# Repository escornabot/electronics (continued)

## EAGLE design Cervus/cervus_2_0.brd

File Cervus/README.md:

# Cervus 2.001

## Catalog

- [Cervus][KEY01] (by [Xdesig][XDE01]) is a 50x50mm board, it controls any Escornabot, and is an atmega development PCB (Arduino Leonardo compatible)

## License

Every content in this repo, otherwise specified under subdirectories, is
licensed under [Creative Commons BY-SA](LICENSE).

## To buy boards

Developers don't produce boards to sell. Under [PCBWAY]

[KEY01]: Keypad
[PCBWAY]: https://www.pcbway.com/project/shareproject/Cervus_Arduino_Leonardo_Coompatible.html
[XDE01]: https://twitter.com/xdesig

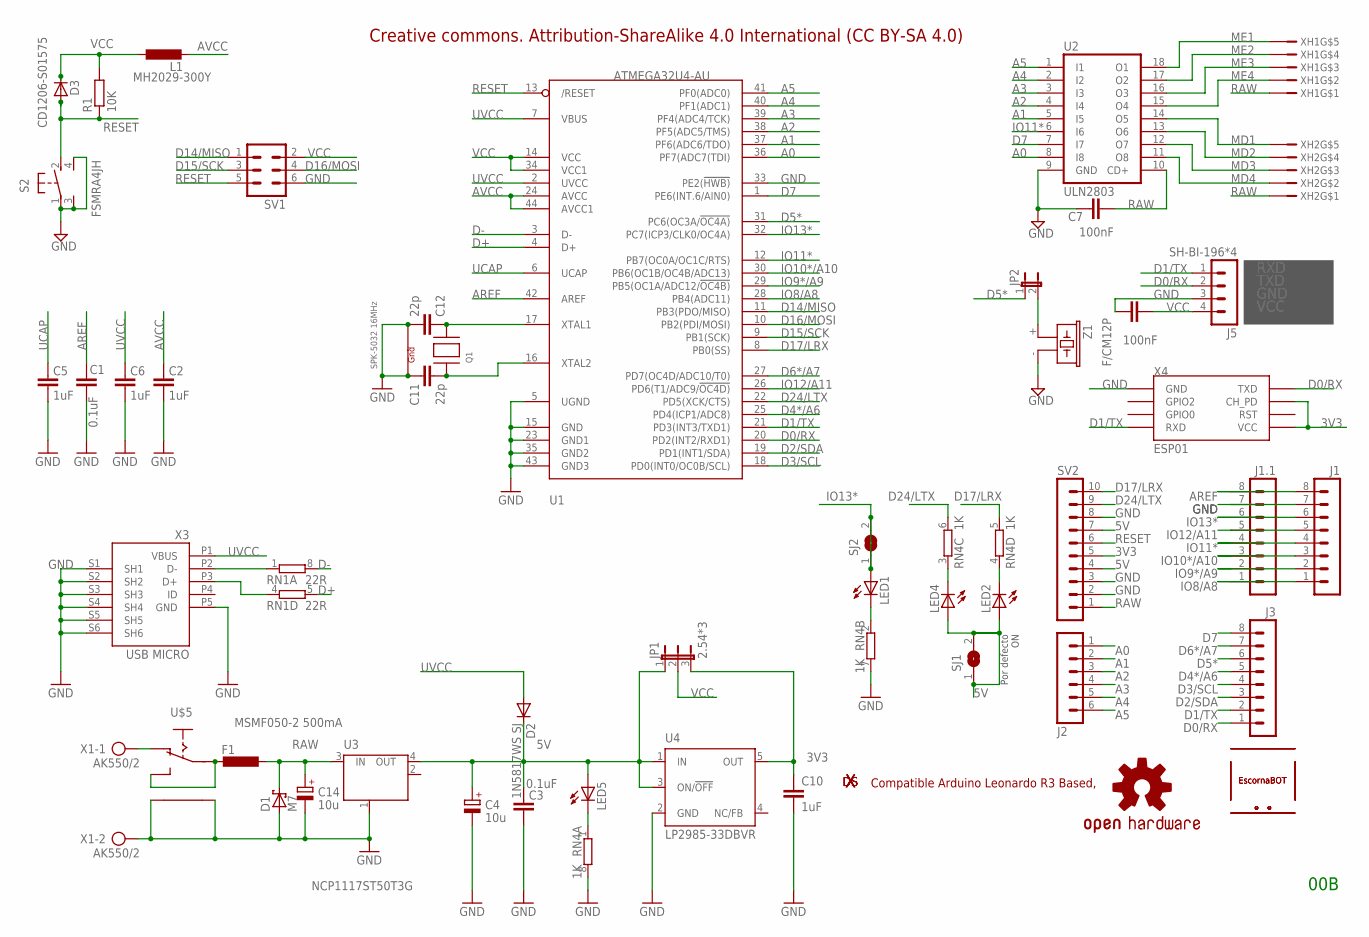
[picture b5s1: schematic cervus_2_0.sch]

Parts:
C1, C3: 0.1uF; 0603-CAP
C2, C5, C6, C10: 1uF; 0603-CAP
C4, C14: 10u; SMC_B
C7, C8: 100nF; C0603K
C11, C12: 22p; C0603-ROUND
D1: M7; SMA
D2: 1N5817WS SJ; SOD-323
D3: CD1206-S01575; MINIMELF
F1: MSMF050-2 500mA; L1812
J1, J1.1, J3: MA08-1
J2: MA06-1
J5: SH-BI-196*4; MA04-1
JP1: 2.54*3; JP2
JP2: JP1E; JP1
L1: MH2029-300Y; R0805
LED1, LED2, LED4, LED5: LEDCHIPLED_0603; CHIPLED_0603
LOGO1: OSHW-LOGOS; OSHW-LOGO-S
Q1: SPK-5032 16MHz; NX3225
R1: 10K; R0603
RN1: 22R; CAY16
RN4: 1K; CAY16
S2: FSMRA4JH; B3F-31XX
SJ1, SJ2: SJ
SV1: MA03-2
SV2: MA10-1
U1: ATMEGA32U4-AU; TQFP44
U2: ULN2803; DIL18
U3: NCP1117ST50T3G; SOT223
U4: LP2985-33DBVR; SOT23-DBV
U$1, U$2: XDESIG; XDESIG_CU_2
U$3, U$4: ESCORNABOT; ESCORNA_PEQUE
U$5: ESCORNA_SK12F14D; ESCORNA_SK-12D07
X1: AK550/2
X3: USB MICRO; CON2_USB_MICRO_B_AT
X4: ESP01
XH1, XH2: XH2.54-5P; B5B-XH-A
Z1: F/CM12P

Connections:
3V3: C10.1, JP1.3, SV2.5, U4.5 (OUT), X4.CH_PD, X4.VCC
5V: C3.2, C4.+, D2.1 (C), JP1.1, LED2.A, LED4.A, LED5.A, SJ1.1, SJ1.2, SV2.4, SV2.7, U3.4 (OUT), U4.1 (IN), U4.3 (ON/!OFF)
A0: J2.1, U1.36 (PF7(ADC7(TDI)), U2.8 (I8)
A1: J2.2, U1.37 (PF6(ADC6/TDO)), U2.5 (I5)
A2: J2.3, U1.38 (PF5(ADC5/TMS)), U2.4 (I4)
A3: J2.4, U1.39 (PF4(ADC4/TCK)), U2.3 (I3)
A4: J2.5, U1.40 (PF1(ADC1)), U2.2 (I2)
A5: J2.6, U1.41 (PF0(ADC0)), U2.1 (I1)
AREF: C1.2, J1.8, J1.1.8, U1.42 (AREF)
AVCC: C2.2, L1.2, U1.24 (AVCC), U1.44 (AVCC1)
D0/RX: J3.1, J5.2, U1.20 (PD2(INT2/RXD1)), X4.TX (TXD)
D1/TX: J3.2, J5.1, U1.21 (PD3(INT3/TXD1)), X4.RX (RXD)
D2/SDA: J3.3, U1.19 (PD1(INT1/SDA))
D3/SCL: J3.4, U1.18 (PD0(INT0/OC0B/SCL))
D4*/A6: J3.5, U1.25 (PD4(ICP1/ADC8))
D5*: J3.6, JP2.1, U1.31 (PC6(OC3A/!OC4A))
D6*/A7: J3.7, U1.27 (PD7(OC4D/ADC10/T0))
D7: J3.8, U1.1 (PE6(INT.6/AIN0)), U2.7 (I7)
D14/MISO: SV1.1, U1.11 (PB3(PDO/MISO))
D15/SCK: SV1.3, U1.9 (PB1(SCK))
D16/MOSI: SV1.4, U1.10 (PB2(PDI/MOSI))
D17/LRX: RN4.5 (2), SV2.10, U1.8 (PB0(SS))
D24/LTX: RN4.6 (2), SV2.9, U1.22 (PD5(XCK/CTS))
D+: RN1.5 (2), U1.4 (D+)
D-: RN1.8 (2), U1.3 (D-)
GND: C1.1, C2.1, C3.1, C4.-, C5.1, C6.1, C7.1, C8.1, C10.2, C11.1, C12.2, C14.-, D1.A, J1.7, J1.1.7, J5.3, Q1.2 (G2), Q1.4 (G1), RN4.7 (2), RN4.8 (2), S2.1, S2.3 (CH2), S2.4 (CH1), SV1.6, SV2.2, SV2.3, SV2.8, U1.5 (UGND), U1.15 (GND), U1.23 (GND1), U1.33 (PE2(!HWB)), U1.35 (GND2), U1.43 (GND3), U2.9 (GND), U3.1 (GND/ADJ), U4.2 (GND), U$5.P$4, U$5.P$5, X1.2, X3.P5 (GND), X3.S1 (SH1), X3.S2 (SH2), X3.S3 (SH3), X3.S4 (SH4), X3.S5 (SH5), X3.S6 (SH6), X4.GND, Z1.- (2)
IO8/A8: J1.1, J1.1.1, U1.28 (PB4(ADC11))
IO9*/A9: J1.2, J1.1.2, U1.29 (PB5(OC1A/ADC12/!OC4B))
IO10*/A10: J1.3, J1.1.3, U1.30 (PB6(OC1B/OC4B/ADC13))
IO11*: J1.4, J1.1.4, U1.12 (PB7(OC0A/OC1C/RTS)), U2.6 (I6)
IO12/A11: J1.5, J1.1.5, U1.26 (PD6(T1/ADC9/!OC4D))
IO13*: J1.6, J1.1.6, LED1.A, SJ2.1, SJ2.2, U1.32 (PC7(ICP3/CLK0/OC4A))
MD1: U2.14 (O5), XH2.P$5
MD2: U2.13 (O6), XH2.P$4
MD3: U2.12 (O7), XH2.P$3
MD4: U2.11 (O8), XH2.P$2
ME1: U2.18 (O1), XH1.P$5
ME2: U2.17 (O2), XH1.P$4
ME3: U2.16 (O3), XH1.P$3
ME4: U2.15 (O4), XH1.P$2
unnamed: LED5.C, RN4.1
unnamed: LED1.C, RN4.2 (1)
unnamed: LED4.C, RN4.3 (1)
unnamed: LED2.C, RN4.4 (1)
unnamed: F1.2, U$5.P$1, U$5.P$3 (S)
unnamed: C11.2, Q1.1 (X1), U1.16 (XTAL2)
unnamed: C12.1, Q1.3 (X2), U1.17 (XTAL1)
unnamed: JP2.2, Z1.+ (1)
unnamed: RN1.1, X3.P2 (D-)
unnamed: RN1.4 (1), X3.P3 (D+)
unnamed: U$5.P$2 (O), X1.1
RAW: C7.2, C14.+, D1.C, F1.1, SV2.1, U2.10 (CD+), U3.3 (IN), XH1.P$1, XH2.P$1
RESET: D3.A, R1.1, S2.2 (S), SV1.5, SV2.6, U1.13 (/RESET)
UCAP: C5.2, U1.6 (UCAP)
UVCC: C6.2, D2.2 (A), U1.2 (UVCC), U1.7 (VBUS), X3.P1 (VBUS)
VCC: C8.2, D3.C, J5.4, JP1.2, L1.1, R1.2, SV1.2, U1.14 (VCC), U1.34 (VCC1)

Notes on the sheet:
RXD
TXD
GND
VCC
00B
Por defecto ON
Creative commons. Attribution-ShareAlike 4.0 International (CC BY-SA 4.0)
Compatible Arduino Leonardo R3 Based,

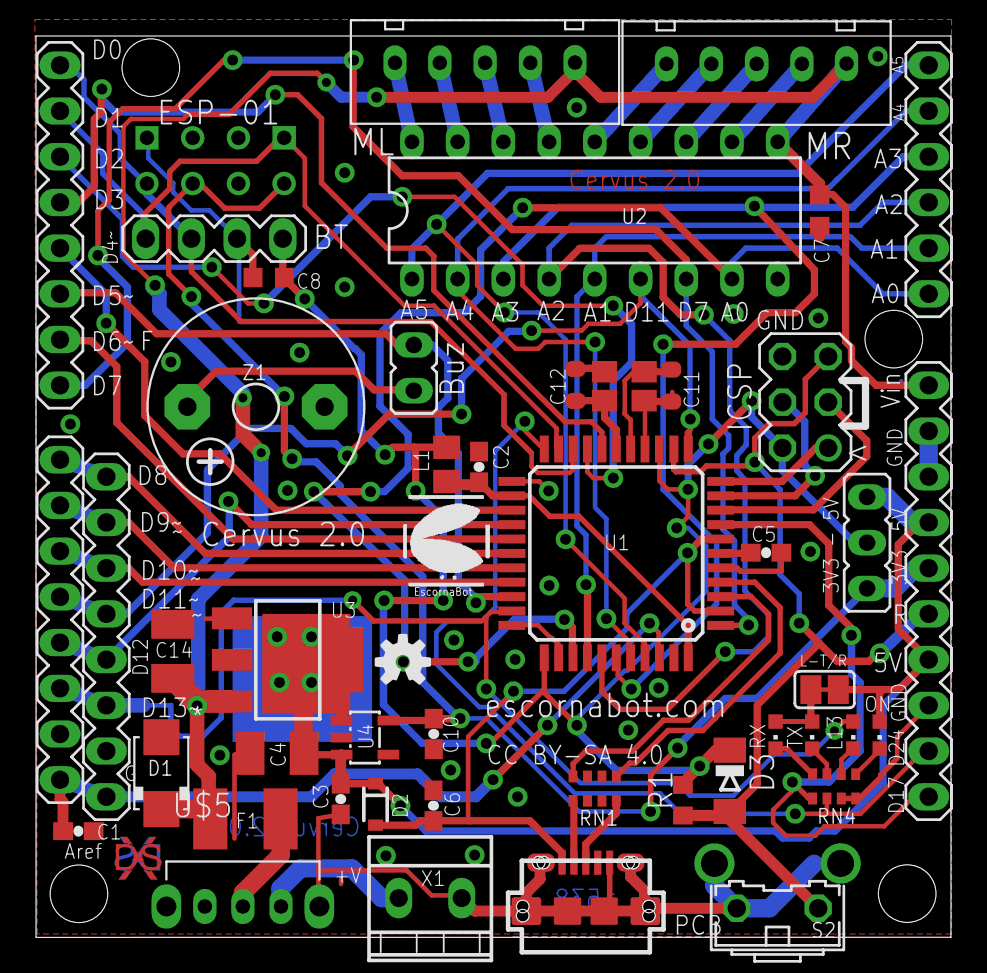
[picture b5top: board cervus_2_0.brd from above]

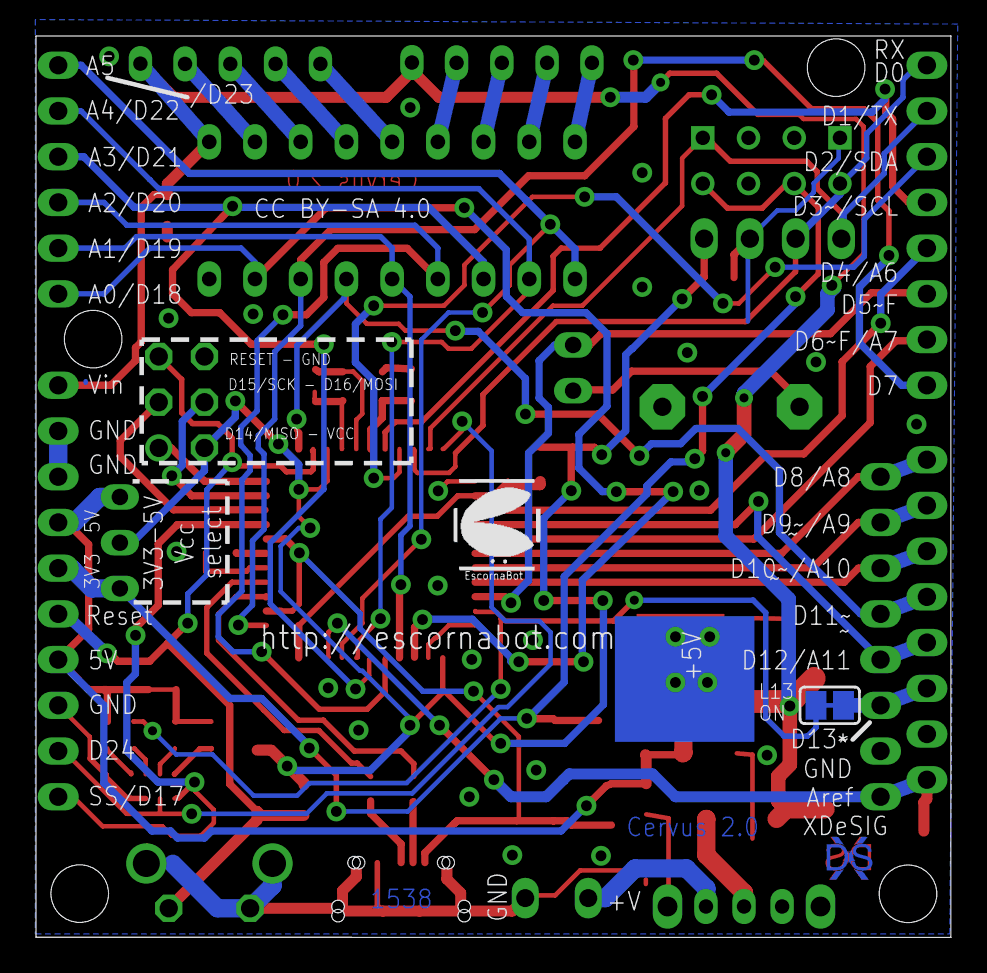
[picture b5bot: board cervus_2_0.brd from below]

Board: 2 copper layers, 50.8 x 50.1 mm, 53 parts (3 on the bottom side), 56 nets.

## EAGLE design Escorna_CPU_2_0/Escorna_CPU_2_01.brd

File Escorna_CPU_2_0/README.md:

# Escorna CPU + Keypad /  (version 2.10)

## Changes 2.10

  - Keyboard pin is A7 instead A4 so I2C interface is free to use in your projects.
  - Polarity inversion protection by diode anti-parallel and resetable fuse.
  - Power switch was moved to better position on the board 'backside'.
  - Switch compatibility with SK-12D07 and SK-12F14.
  - Keypad can use tactile switches 6mm, 12mm and 12mm with LED. See more below.
  - One of the EscornaShield connector was removed (obsolete).
  - Continuing the connector D13 - RAW (expand connections)
  - Buzzer, power connectors and drivers can be connected on both sides of the board.
  - Holes for holders continue in the same position (PCB extended 5.1mm backwards).
  - Full compatible one side, with an operative Escornabot (excepting the expansion connector).

## Tactile switches with LED

LED assignments:    --        [suggested color][wiki]

| KEY / signal| Color |
|-------------|-------|
| UP  / A0    | Blue  |
| RIGHT / A3  | Gren  |
| DOWN / A2   | Yelow |
| LEFT / A1   | Reed  |
| GO / D13    | WiteA |

The LEDs can be disabled by cutting a small wire-jumper, you can use these outputs for other things. Reconnect with a small welding.

## Expansion connector

2.54mm double strip

|   row 1         |     row 2      |
|-----------------|----------------|
| 3V3             | 3V3            |
| 5V              | 5V             |
| D13 / SCK       | A0 / D14       |
| A1  / D15       | A2 / D16       |
| A3  / D17       | A4 / D18 / SDA |
| A5  / D19 / SCL | A6 / No Pullup |
| GND             | GND            |
|-----------------|----------------|

## Author and license

* Author: [XDeSIG][TWI01]
* License: [Creative Commons BY-SA][CCBYSA]

![Render Escorna CPU 2.10][RENDER]

<!-- links -->
[wiki]: https://en.wikipedia.org/wiki/Navigation_light
[CCBYSA]: http://creativecommons.org/licenses/by-sa/4.0/
[TWI01]: https://twitter.com/xdesig
[RENDER]: Escorna_CPU_2_10_34T.jpg

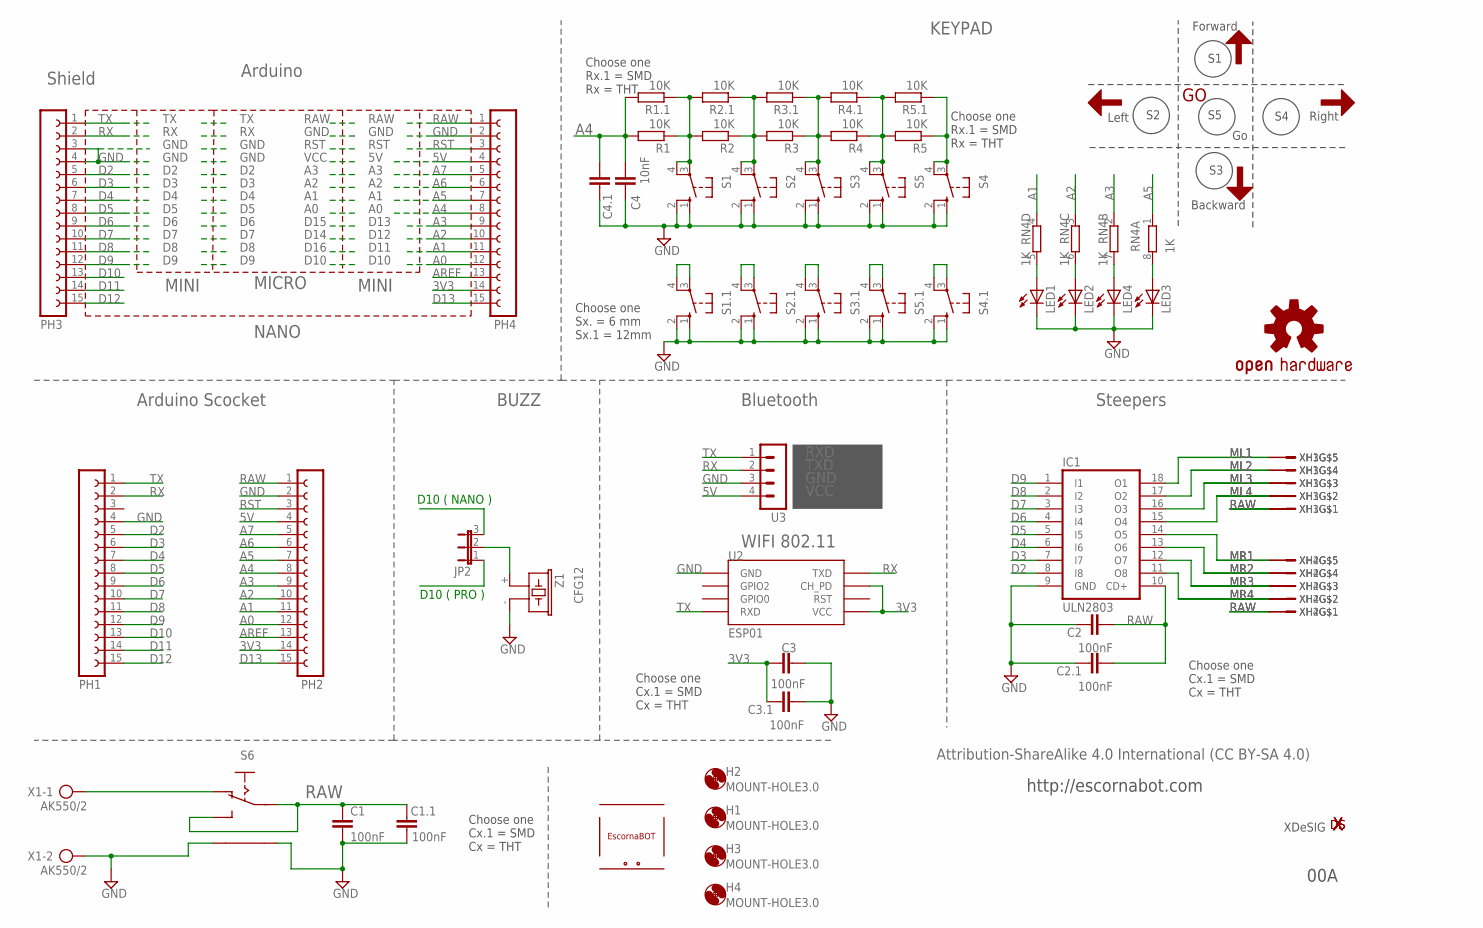
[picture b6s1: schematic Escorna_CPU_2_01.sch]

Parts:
C1, C2, C3: 100nF; C025-025X050
C1.1, C2.1, C3.1: 100nF; C0603
C4: 10nF; C025-025X050
C4.1: 10nF; C0603
ESC: ESCORNABOT; ESCORNA_PEQUE
H1, H2, H3, H4: MOUNT-HOLE3.0; 3,0
IC1: ULN2803; DIL18
JP2: JP2E; JP2
LED1, LED2, LED3, LED4: LED_ESML0603; LED_SML0603
LOGO2: OSHW-LOGOS; OSHW-LOGO-S
PH1, PH2, PH3, PH4: FE15-1; FE15
R1, R2, R3, R4, R5: 10K; 0204/7
R1.1, R2.1, R3.1, R4.1, R5.1: 10K; R0603
RN4: 1K; CAY16
S1, S2, S3, S4, S5: 10-XX; B3F-10XX
S1.1, S2.1, S3.1, S4.1, S5.1: SWITCH-OMRON_40-XX; SWITCH-OMRON_B3F40XX_NH
S6: SK12F14D; SK-12D07
U2: ESP01
U3: MA04-1
U$1, U$3, U$6, U$11: FRECHA
U$2: GO; VALE
U$12: XDESIG_XDESIG21; XDESIG_XDESIG
X1: AK550/2
XDS1: XDESIG; XDESIG_CU_2
XH1, XH2, XH3, XH4: B5B-XH-A
Z1: CFG12; F/CM12P

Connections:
3V3: C3.1, C3.1.1, PH2.14, PH4.14, U2.CH_PD, U2.VCC
5V: PH2.4, PH4.4, U3.4
A0: JP2.1, PH2.12, PH4.12
A1: PH2.11, PH4.11, RN4.4 (1)
A2: PH2.10, PH4.10, RN4.3 (1)
A3: PH2.9, PH4.9, RN4.2 (1)
A4: C4.2, C4.1.2, PH2.8, PH4.8, R1.2, R1.1.2
A5: PH2.7, PH4.7, RN4.1
A6: PH2.6, PH4.6
A7: PH2.5, PH4.5
AREF: PH2.13, PH4.13
D2: IC1.8 (I8), PH1.5, PH3.5
D3: IC1.7 (I7), PH1.6, PH3.6
D4: IC1.6 (I6), PH1.7, PH3.7
D5: IC1.5 (I5), PH1.8, PH3.8
D6: IC1.4 (I4), PH1.9, PH3.9
D7: IC1.3 (I3), PH1.10, PH3.10
D8: IC1.2 (I2), PH1.11, PH3.11
D9: IC1.1 (I1), PH1.12, PH3.12
D10: JP2.3, PH1.13, PH3.13
D11: PH1.14, PH3.14
D12: PH1.15, PH3.15
D13: PH2.15, PH4.15
GND: C1.2, C1.1.1, C2.1, C2.1.1, C3.2, C3.1.2, C4.1, C4.1.1, IC1.9 (GND), LED1.C, LED2.C, LED3.C, LED4.C, PH1.4, PH2.2, PH3.3, PH3.4, PH4.2, S1.1 (S), S1.2 (S1), S1.1.1 (S), S1.1.2 (S1), S2.1 (S), S2.2 (S1), S2.1.1 (S), S2.1.2 (S1), S3.1 (S), S3.2 (S1), S3.1.1 (S), S3.1.2 (S1), S4.1 (S), S4.2 (S1), S4.1.1 (S), S4.1.2 (S1), S5.1 (S), S5.2 (S1), S5.1.1 (S), S5.1.2 (S1), S6.P$4, S6.P$5, U2.GND, U3.3, X1.2, Z1.- (2)
ML1: IC1.18 (O1), XH1.P$5, XH3.P$5
ML2: IC1.17 (O2), XH1.P$4, XH3.P$4
ML3: IC1.16 (O3), XH1.P$3, XH3.P$3
ML4: IC1.15 (O4), XH1.P$2, XH3.P$2
MR1: IC1.14 (O5), XH2.P$5, XH4.P$5
MR2: IC1.13 (O6), XH2.P$4, XH4.P$4
MR3: IC1.12 (O7), XH2.P$3, XH4.P$3
MR4: IC1.11 (O8), XH2.P$2, XH4.P$2
unnamed: JP2.2, Z1.+ (1)
unnamed: S6.P$2 (O), X1.1
unnamed: LED1.A, RN4.5 (2)
unnamed: LED2.A, RN4.6 (2)
unnamed: LED4.A, RN4.7 (2)
unnamed: LED3.A, RN4.8 (2)
RAW: C1.1, C1.1.2, C2.2, C2.1.2, IC1.10 (CD+), PH2.1, PH4.1, S6.P$1, S6.P$3 (S), XH1.P$1, XH2.P$1, XH3.P$1, XH4.P$1
RST: PH2.3, PH4.3
RX: PH1.2, PH3.2, U2.TX (TXD), U3.2
S1: R1.1, R1.1.1, R2.2, R2.1.2, S1.3, S1.4 (P1), S1.1.3, S1.1.4 (P1)
S2: R2.1, R2.1.1, R3.2, R3.1.2, S2.3, S2.4 (P1), S2.1.3, S2.1.4 (P1)
S3: R3.1, R3.1.1, R4.2, R4.1.2, S3.3, S3.4 (P1), S3.1.3, S3.1.4 (P1)
S4: R4.1, R4.1.1, R5.2, R5.1.2, S5.3, S5.4 (P1), S5.1.3, S5.1.4 (P1)
S5: R5.1, R5.1.1, S4.3, S4.4 (P1), S4.1.3, S4.1.4 (P1)
TX: PH1.1, PH3.1, U2.RX (RXD), U3.1

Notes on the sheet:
Arduino Scocket
Steepers
KEYPAD
BUZZ
Bluetooth
RXD
TXD
GND
VCC
D10 ( NANO )
D10 ( PRO )
Shield
NANO
Arduino
MINI
MICRO
RAW
RST
D13
D15
D12
D14
D11
D16
D10
Attribution-ShareAlike 4.0 International (CC BY-SA 4.0)
Forward
Left
Right
Backward
WIFI 802.11
Choose one Rx.1 = SMD Rx = THT
Choose one Cx.1 = SMD Cx = THT
XDeSIG
http://escornabot.com
Choose one Sx. = 6 mm Sx.1 = 12mm
00A

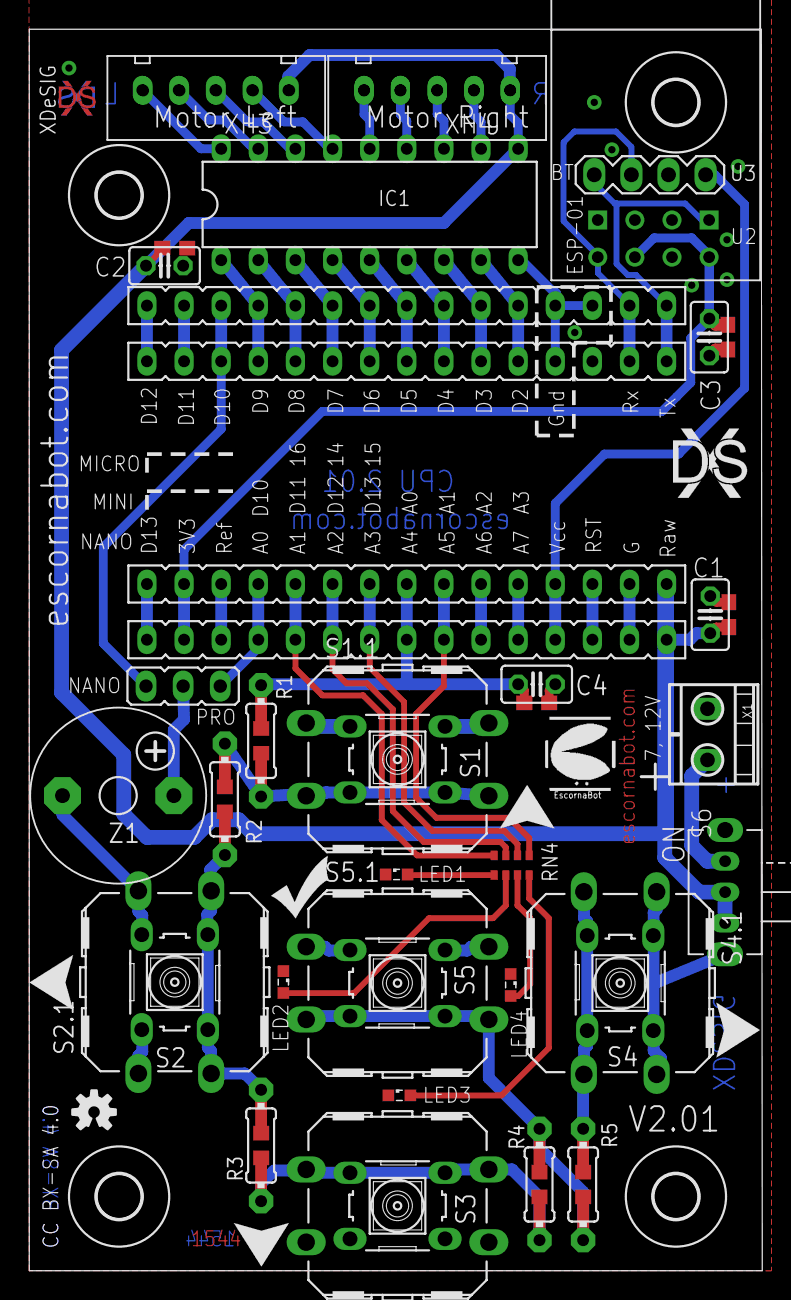
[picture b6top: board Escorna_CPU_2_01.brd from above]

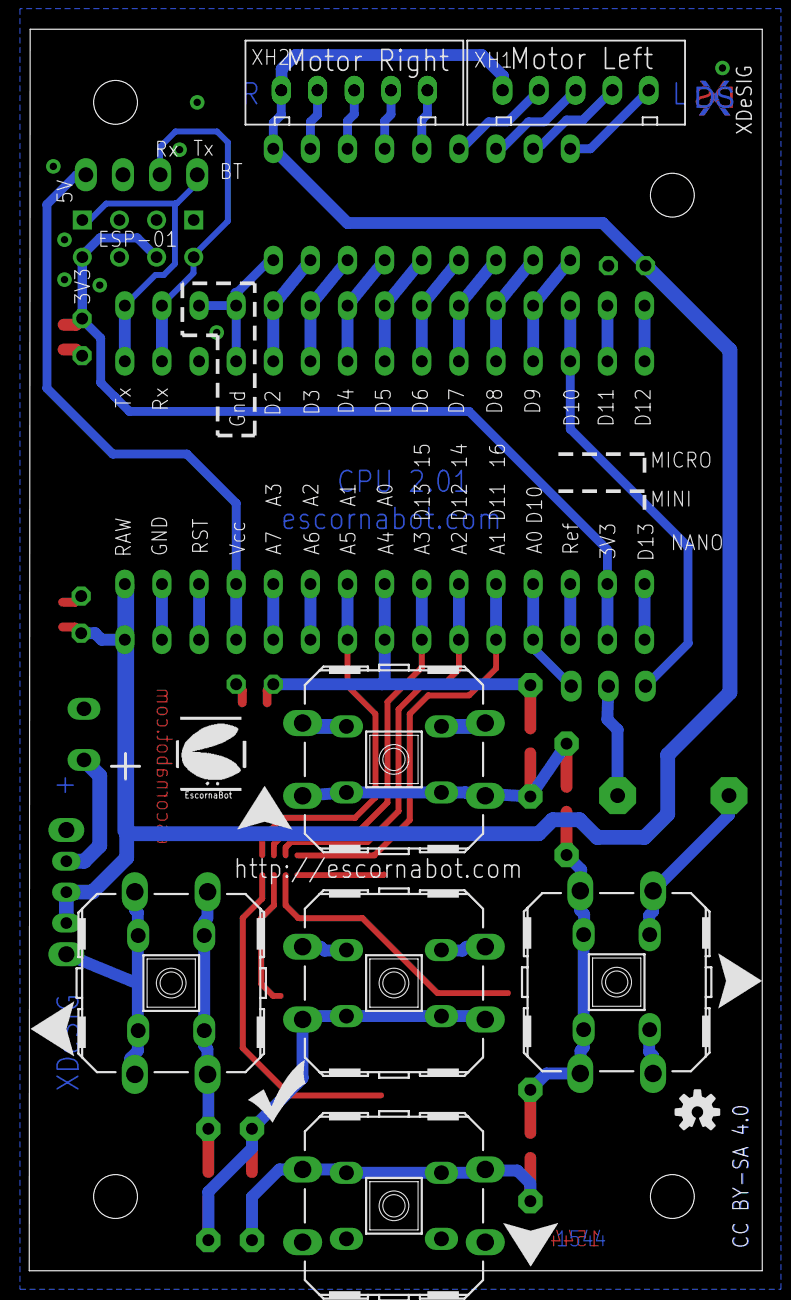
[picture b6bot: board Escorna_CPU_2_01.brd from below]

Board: 2 copper layers, 50.2 x 85.0 mm, 69 parts (10 on the bottom side), 47 nets.

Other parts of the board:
LOGO1: OSHW-LOGOS; OSHW-LOGO-S
U$4, U$7, U$8, U$9: FRECHA
U$5: ESCORNABOT; ESCORNA_PEQUE
U$10: GO; VALE
XDS: XDESIG; XDESIG_CU_2

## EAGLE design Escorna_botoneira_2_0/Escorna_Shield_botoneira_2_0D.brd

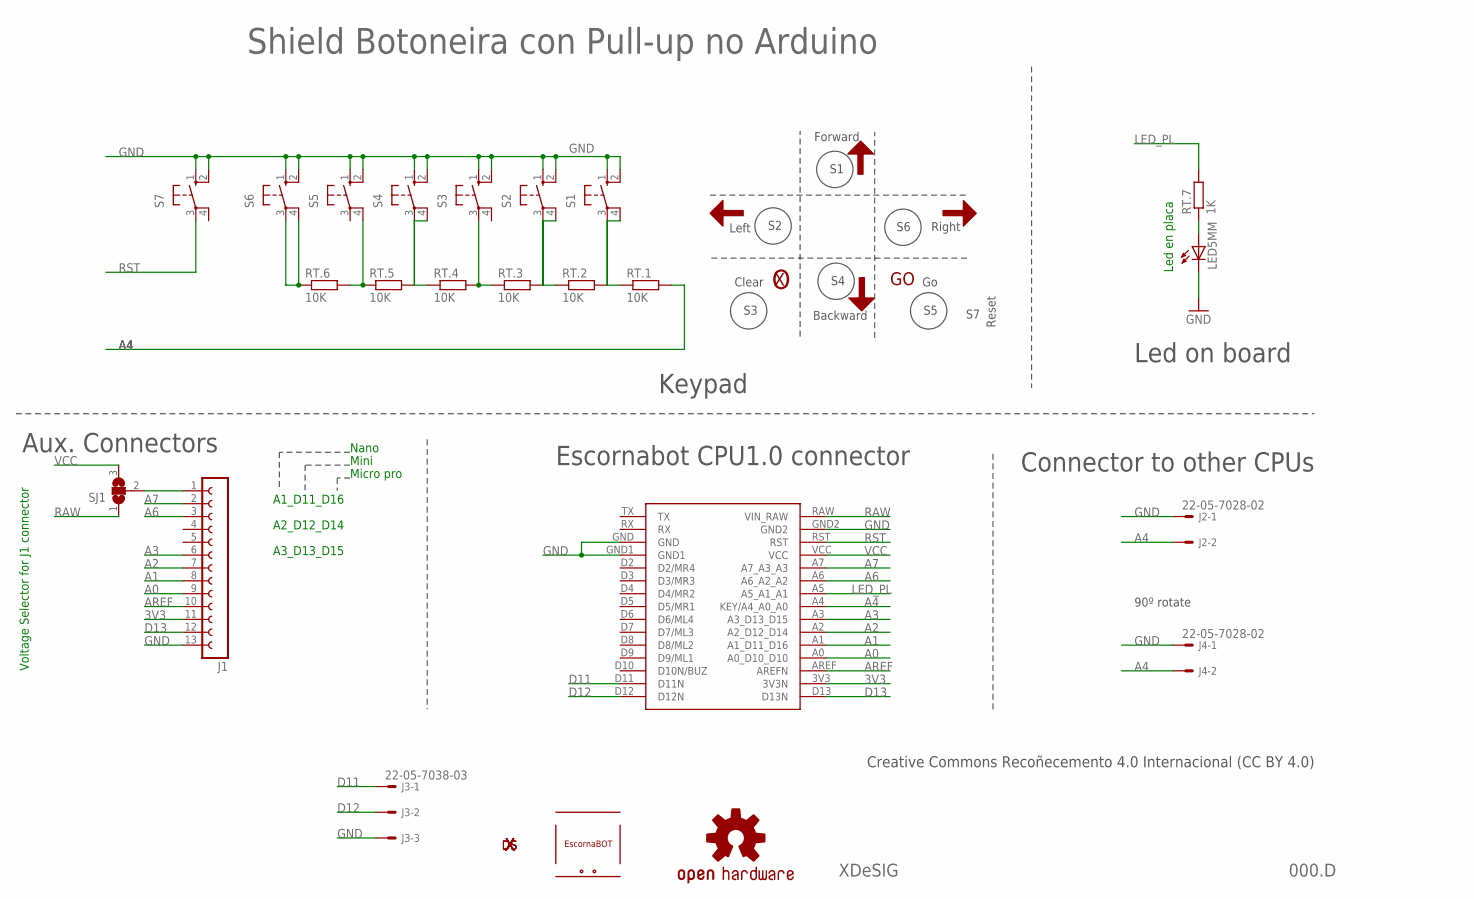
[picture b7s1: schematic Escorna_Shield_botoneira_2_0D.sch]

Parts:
ESSH1: OUTL_ESCORNASHILED; OUTL_ESCORNASHIELD
J1: FE13-1; FE13
J2, J4: 22-05-7028-02; 7395-02
J3: 22-05-7038-03; 7395-03
LED5MM: LED5MM
LOGO2: OSHW-LOGOS; OSHW-LOGO-S
RT.1, RT.2, RT.3, RT.4, RT.5, RT.6: 10K; 0204/7
RT.7: 1K; 0204/7
S1, S2, S3, S4, S5, S6: B3F-40XX; B3F40XX_NH
S7: 10-XX; B3F-10XX
SJ1: SOLDERJUMPER_2WAY; SJ_2
U$1: ESCORNABOT; ESCORNA_PEQUE
U$3: XDESIG21; XDESIG
U$4, U$5, U$6, U$7: FRECHA
U$8: GO; VALE
U$9: CANCELA; ASPA
U$10: XDESIG; XDESIG_CU_2

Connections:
3V3: ESSH1.3V3 (3V3N), J1.11
A0: ESSH1.A0 (A0_D10_D10), J1.9
A1: ESSH1.A1 (A1_D11_D16), J1.8
A2: ESSH1.A2 (A2_D12_D14), J1.7
A3: ESSH1.A3 (A3_D13_D15), J1.6
A4: ESSH1.A4 (KEY/A4_A0_A0), J2.2, J4.2, RT.1.2
A6: ESSH1.A6 (A6_A2_A2), J1.3
A7: ESSH1.A7 (A7_A3_A3), J1.2
AREF: ESSH1.AREF (AREFN), J1.10
D11: ESSH1.D11 (D11N), J3.1
D12: ESSH1.D12 (D12N), J3.2
D13: ESSH1.D13 (D13N), J1.12
GND: ESSH1.GND, ESSH1.GND1, ESSH1.GND2, J1.13, J2.1, J3.3, J4.1, LED5MM.K (C), S1.1 (S), S1.2 (S1), S2.1 (S), S2.2 (S1), S3.1 (S), S3.2 (S1), S4.1 (S), S4.2 (S1), S5.1 (S), S5.2 (S1), S6.1 (S), S6.2 (S1), S7.1 (S), S7.2 (S1)
LED_PL: ESSH1.A5 (A5_A1_A1), RT.7.2
unnamed: LED5MM.A, RT.7.1
unnamed: J1.1, SJ1.2
unnamed: RT.2.2, S1.4 (P1)
unnamed: RT.1.1, S1.3
unnamed: RT.5.2, S4.4 (P1)
unnamed: RT.6.1, S6.3, S6.4 (P1)
unnamed: RT.4.1, S4.3
unnamed: RT.3.1, RT.4.2, S3.3
unnamed: RT.2.1, S2.3
unnamed: RT.3.2, S2.4 (P1)
unnamed: RT.5.1, RT.6.2, S5.4 (P1)
RAW: ESSH1.RAW (VIN_RAW), SJ1.1
RST: ESSH1.RST, S7.3
VCC: ESSH1.VCC, SJ1.3

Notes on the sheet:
Shield Botoneira con Pull-up no Arduino
000.D
XDeSIG
Forward
Left
Right
Backward
Clear
Led en placa
A1_D11_D16
A2_D12_D14
A3_D13_D15
Voltage Selector for J1 connector
Reset
Led on board
Keypad
Escornabot CPU1.0 connector
Connector to other CPUs
Aux. Connectors
Nano
Mini
Micro pro
90º rotate
Creative Commons Recoñecemento 4.0 Internacional (CC BY 4.0)

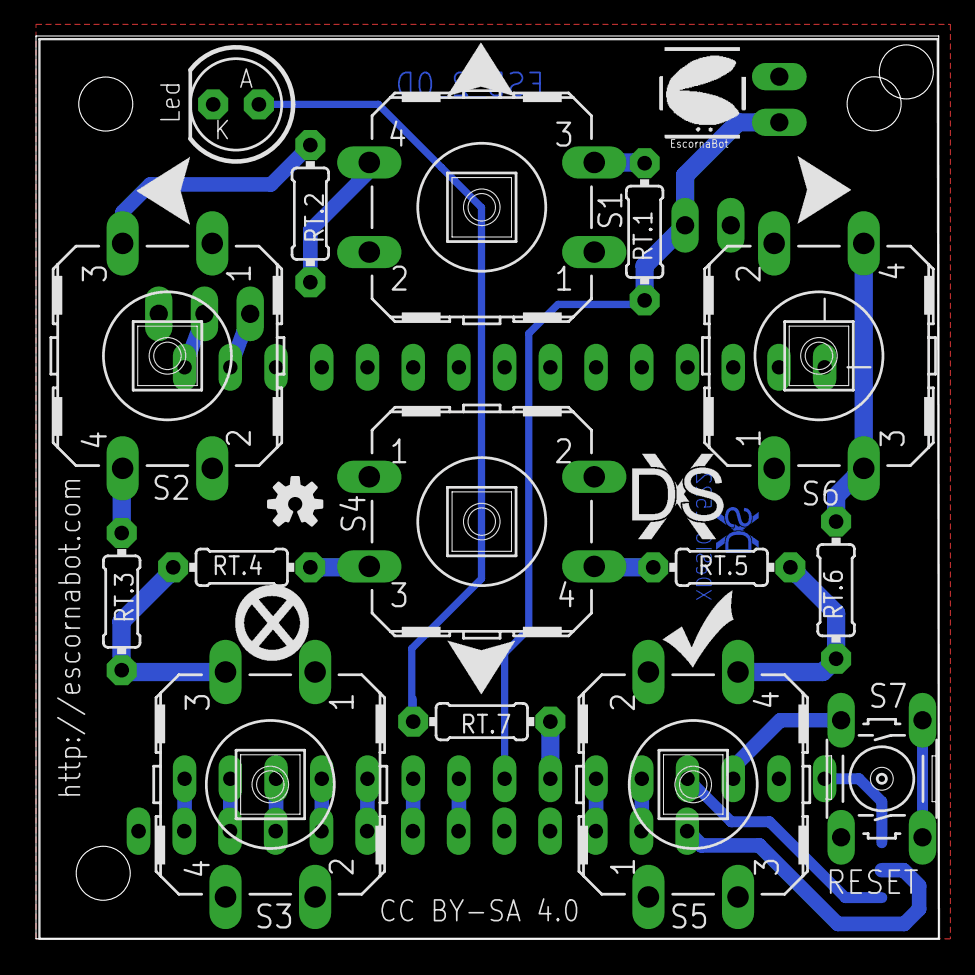
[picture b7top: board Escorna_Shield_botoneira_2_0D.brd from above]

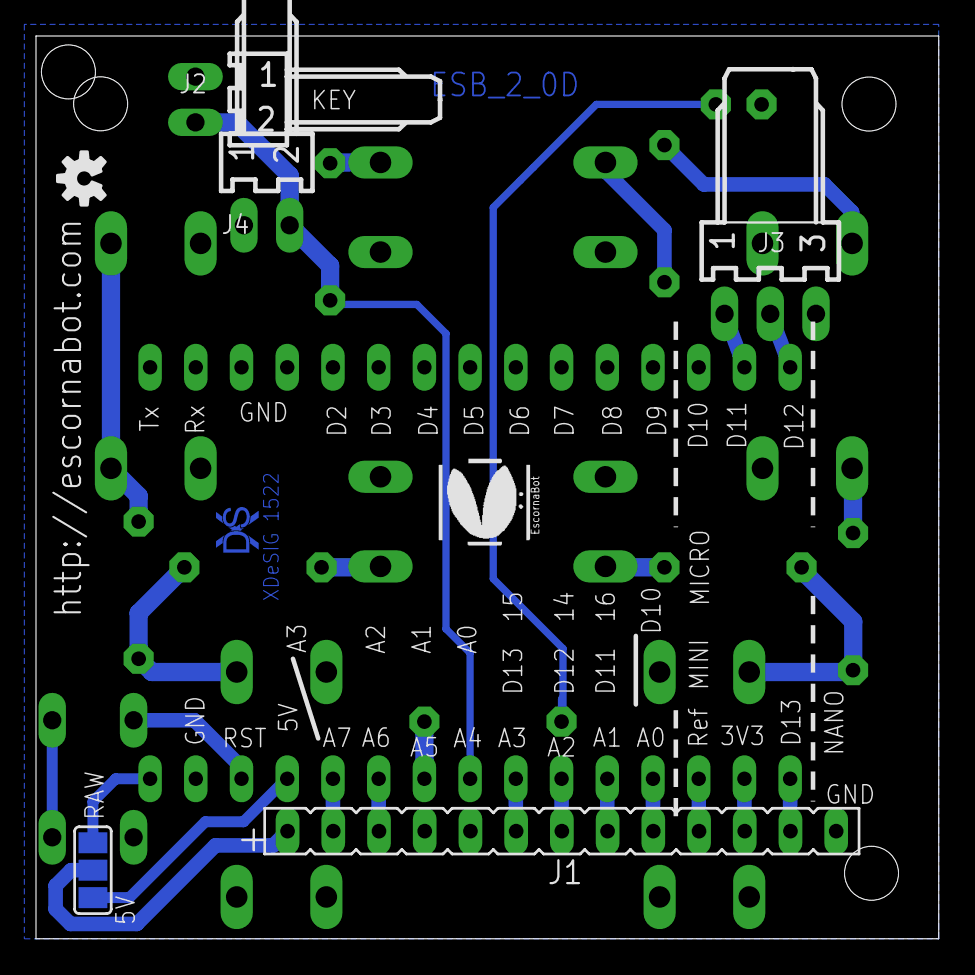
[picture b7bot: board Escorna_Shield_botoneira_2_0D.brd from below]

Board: 2 copper layers, 50.2 x 50.2 mm, 33 parts (8 on the bottom side), 28 nets.

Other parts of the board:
LOGO1: OSHW-LOGOS; OSHW-LOGO-S
U$2: ESCORNABOT; ESCORNA_PEQUE

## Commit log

2015-05-12 Escorna CPU 1.0
    Vesion para pinchar Arduinos NANO e MICRO
2015-05-12 Borrado os ficheiros non necesarios
2015-05-12 Revert "Borrado os ficheiros non necesarios"
    This reverts commit f0e8e139e9fdb07a18cae6f65af2a35986a8202c.
2015-05-12 Revert "Revert "Borrado os ficheiros non necesarios""
    This reverts commit 489b6fce32a890dd59943b3321fc677716cee3f6.
2015-05-15 engadidos
    novas placas engadidas
2015-05-15 Esquema actualizado
2015-05-16 Proposta CERVUS 1.0
    Escorna cpu 2.01 a Cervus 1.0. Pendente de test!
2015-06-03 Melloras
    Melloras Botoneira a 2.0C
    CPU a 1.01
2015-06-03 Pedir placas en IMALL
    procedemento para pedir placas en IMall
2015-06-04 Xdesig update 2015-06-04
2015-07-22 Version D
2015-07-22 Versión 2.0D
2015-07-22 Actualización nome
    comprobado e funcional
2015-07-22 Docus
2015-08-04 Placa unificada
    Soporte para arduino (nano...) e Teclado nunha PCB
2015-09-19 Act. bottom layer
2015-09-22 Act. slikscreen
2015-10-27 error in layer top resolve
2015-10-27 "D" Version
    3mm holes
2015-10-28 isolate to 0.4mm
    facility to DiY
2015-11-19 Act S6 library
2015-11-21 Actualizando a 2.0
2015-11-21 Cervus 2.0
2016-04-13 New EscornaBot CPU 2.10
2016-04-13 Change texts
2016-04-13 short
2016-04-13 Adjust text
2016-04-13 Arrange tex
2016-07-07 2.10
2016-07-29 new values
    New values of resistors, (R5) for the switch S5 and (R10) improves the
    brightness of the green LED.
2017-02-23 Directories refactoring.
2017-02-23 README as index of repository.
2017-02-23 Board credits.
2017-02-23 Providers directory.
2017-06-11 EscornaCPU 2.12 by XDesig.
2018-04-19 New design
2018-04-19 Add Keypad 2.1
2018-04-29 New docus
2018-04-29 new documentation
2018-05-05 Attribution-ShareAlike 4.0 International (CC BY-SA 4.0)
2018-07-05 Upgrade
    cambios en 2.20
2018-07-05 Upgrade
    Resolve bug
2018-07-06 Update
    Pass
2018-07-06 Update
    Remove unnecessary files
2020-10-14 Up 2.40
2021-10-25 Update license
2022-01-19 Update test teclado
2023-03-12 Update links
